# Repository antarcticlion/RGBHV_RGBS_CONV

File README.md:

# RGB MULTI CONV

Display/Monitor video signal converter PCB for Japanese Retro PC (RGBHV &lt;--> RGBS ./ etc. )

##概要

主に日本製のレトロPCのRGB信号を、コネクタ変換・信号変換・分岐を行うボードです。
Rev1.5でサブボードをスタックして扱うコネクタを増やせるようにしています。
プロジェクトにはKiCad PCB 5.0用のプロジェクトファイルとガーバーが含まれます。

##外観

## 動作確認済機種
### Video signal src.
- IBM-PC compatible (VGA)  
- PC-8801mk2 (Digital RGB 8p)  
- PC-8801mk2MR/FH (Digital RGB 8p/Analog RGB DA15)  
- PC-9801DA/U2 (Analog RGB DA15)  
- PC-9801VX41 (Digital RGB 8p/Analog RGB DA15)  
- X1 Turbo model40 (Digital RGB 8p)  
- X1 Turbo model30 (Digital RGB 6p)  
- MZ-700 (Digital RGB 8p)  
- FM-7 (Digital RGB 8p)  
- FM-new7 (Digital RGB 8p)  
- BASIC Master Level 3 (Digital RGB 8p)  
- Arcade-Game PCBs (クイズココロジー2／上海2／子育てクイズ マイエンジェル）(信号分岐、コネクタ変換)
- 上記の他、PC8001シリーズ(Digital RGB)で動作報告をいただいております。ありがとうございます。
### Video signal dst.
- GBS-8200/GBS-8220/HD9800V/HD-VC9900(RGBS)
- Some VGA monitors (DE15/VGA)

***
[概要](https://github.com/antarcticlion/RGBHV_RGBS_CONV/wiki)  
[作り方](https://github.com/antarcticlion/RGBHV_RGBS_CONV/wiki/How-to-make)  
[デザインと説明](https://github.com/antarcticlion/RGBHV_RGBS_CONV/wiki/Design)  
[その他](https://github.com/antarcticlion/RGBHV_RGBS_CONV/wiki/Miscellaneous)  
[リリースノート](https://github.com/antarcticlion/RGBHV_RGBS_CONV/wiki/Release-note)  

***
最新版 Rev1.5A

***
# Lastest Gerber

### 1.5A  
https://github.com/antarcticlion/RGBHV_RGBS_CONV/blob/master/RGBHV_RGBS_CONV_15A.zip メインボード
https://github.com/antarcticlion/RGBHV_RGBS_CONV/blob/master/RGBHV_RGBS_CONV_EXTRA1_15.zip　デジタルRGBサブボード
https://github.com/antarcticlion/RGBHV_RGBS_CONV/blob/master/RGBHV_RGBS_CONV_stack_15.zip　GBSスタック用サブボード

## Arcive

### 1.0D  
https://github.com/antarcticlion/RGBHV_RGBS_CONV/blob/master/RGBHV_RGBS_CONV_10D.zip

***
# Changes Log  
| Revision | Date | Description |
|:---|:---|:---|
|1.5A release |2022/10/03 | スイッチのスルーホールサイズを変更 |
|1.5 release candidate |2022/09/23 | DE15/DA15を残し他のコネクタは小基板化、EL1883用パターンを追加、各種切り替えスイッチを付ける |
||2022/09/23 | 最新のガーバーファイルを残して古いものは削除 |
|1.0D release |2021/07/29 | DIN8コネクタのフットプリントが裏表逆になっていたのをFIX |
|1.0C release |2021/07/09 | RGBSへの音声パターンカット、レギュレータの足配置バリエーションの追加 |
|1.0B release |2021/05/11 | 3.3Vレギュレータによる電源安定化、3.3V駆動の5VトレラントCMOSロジックでGBS出力の無調整化(SN74AHC86N推奨) |
|0.5B release |2020/06/10 | RGBS出力に多回転VRを追加し、出力レベルを下げられるコネクタを用意。(GBS8200/8220のCSYNC信号不安定対策) |
|0.5A release |2019/08/28 | あまり使わないコネクタと、動悸分離回路を削除、RGBHV DA15のエッジ端コネクタを追加 |
|0.4A release candidate |2019/03/04 | コネクタ位置調整、DCジャック追加 |
|0.4 |2019/03/04 | first release. (experimental) |
|0.1～0.3 | N/A | private |

***
# ライセンス

2022/06/04 
Rev1.0D以降のライセンスを CERN Open Hardware Licence Version 2 - Weakly Reciprocal に変更します。
以前のバージョンのアーカイブは近日消します。

https://spdx.org/licenses/CERN-OHL-W-2.0.html
PDF https://github.com/antarcticlion/RGBHV_RGBS_CONV/blob/master/cern_ohl_w_v2.pdf
HOWTO https://github.com/antarcticlion/RGBHV_RGBS_CONV/blob/master/cern_ohl_w_v2_howto.pdf

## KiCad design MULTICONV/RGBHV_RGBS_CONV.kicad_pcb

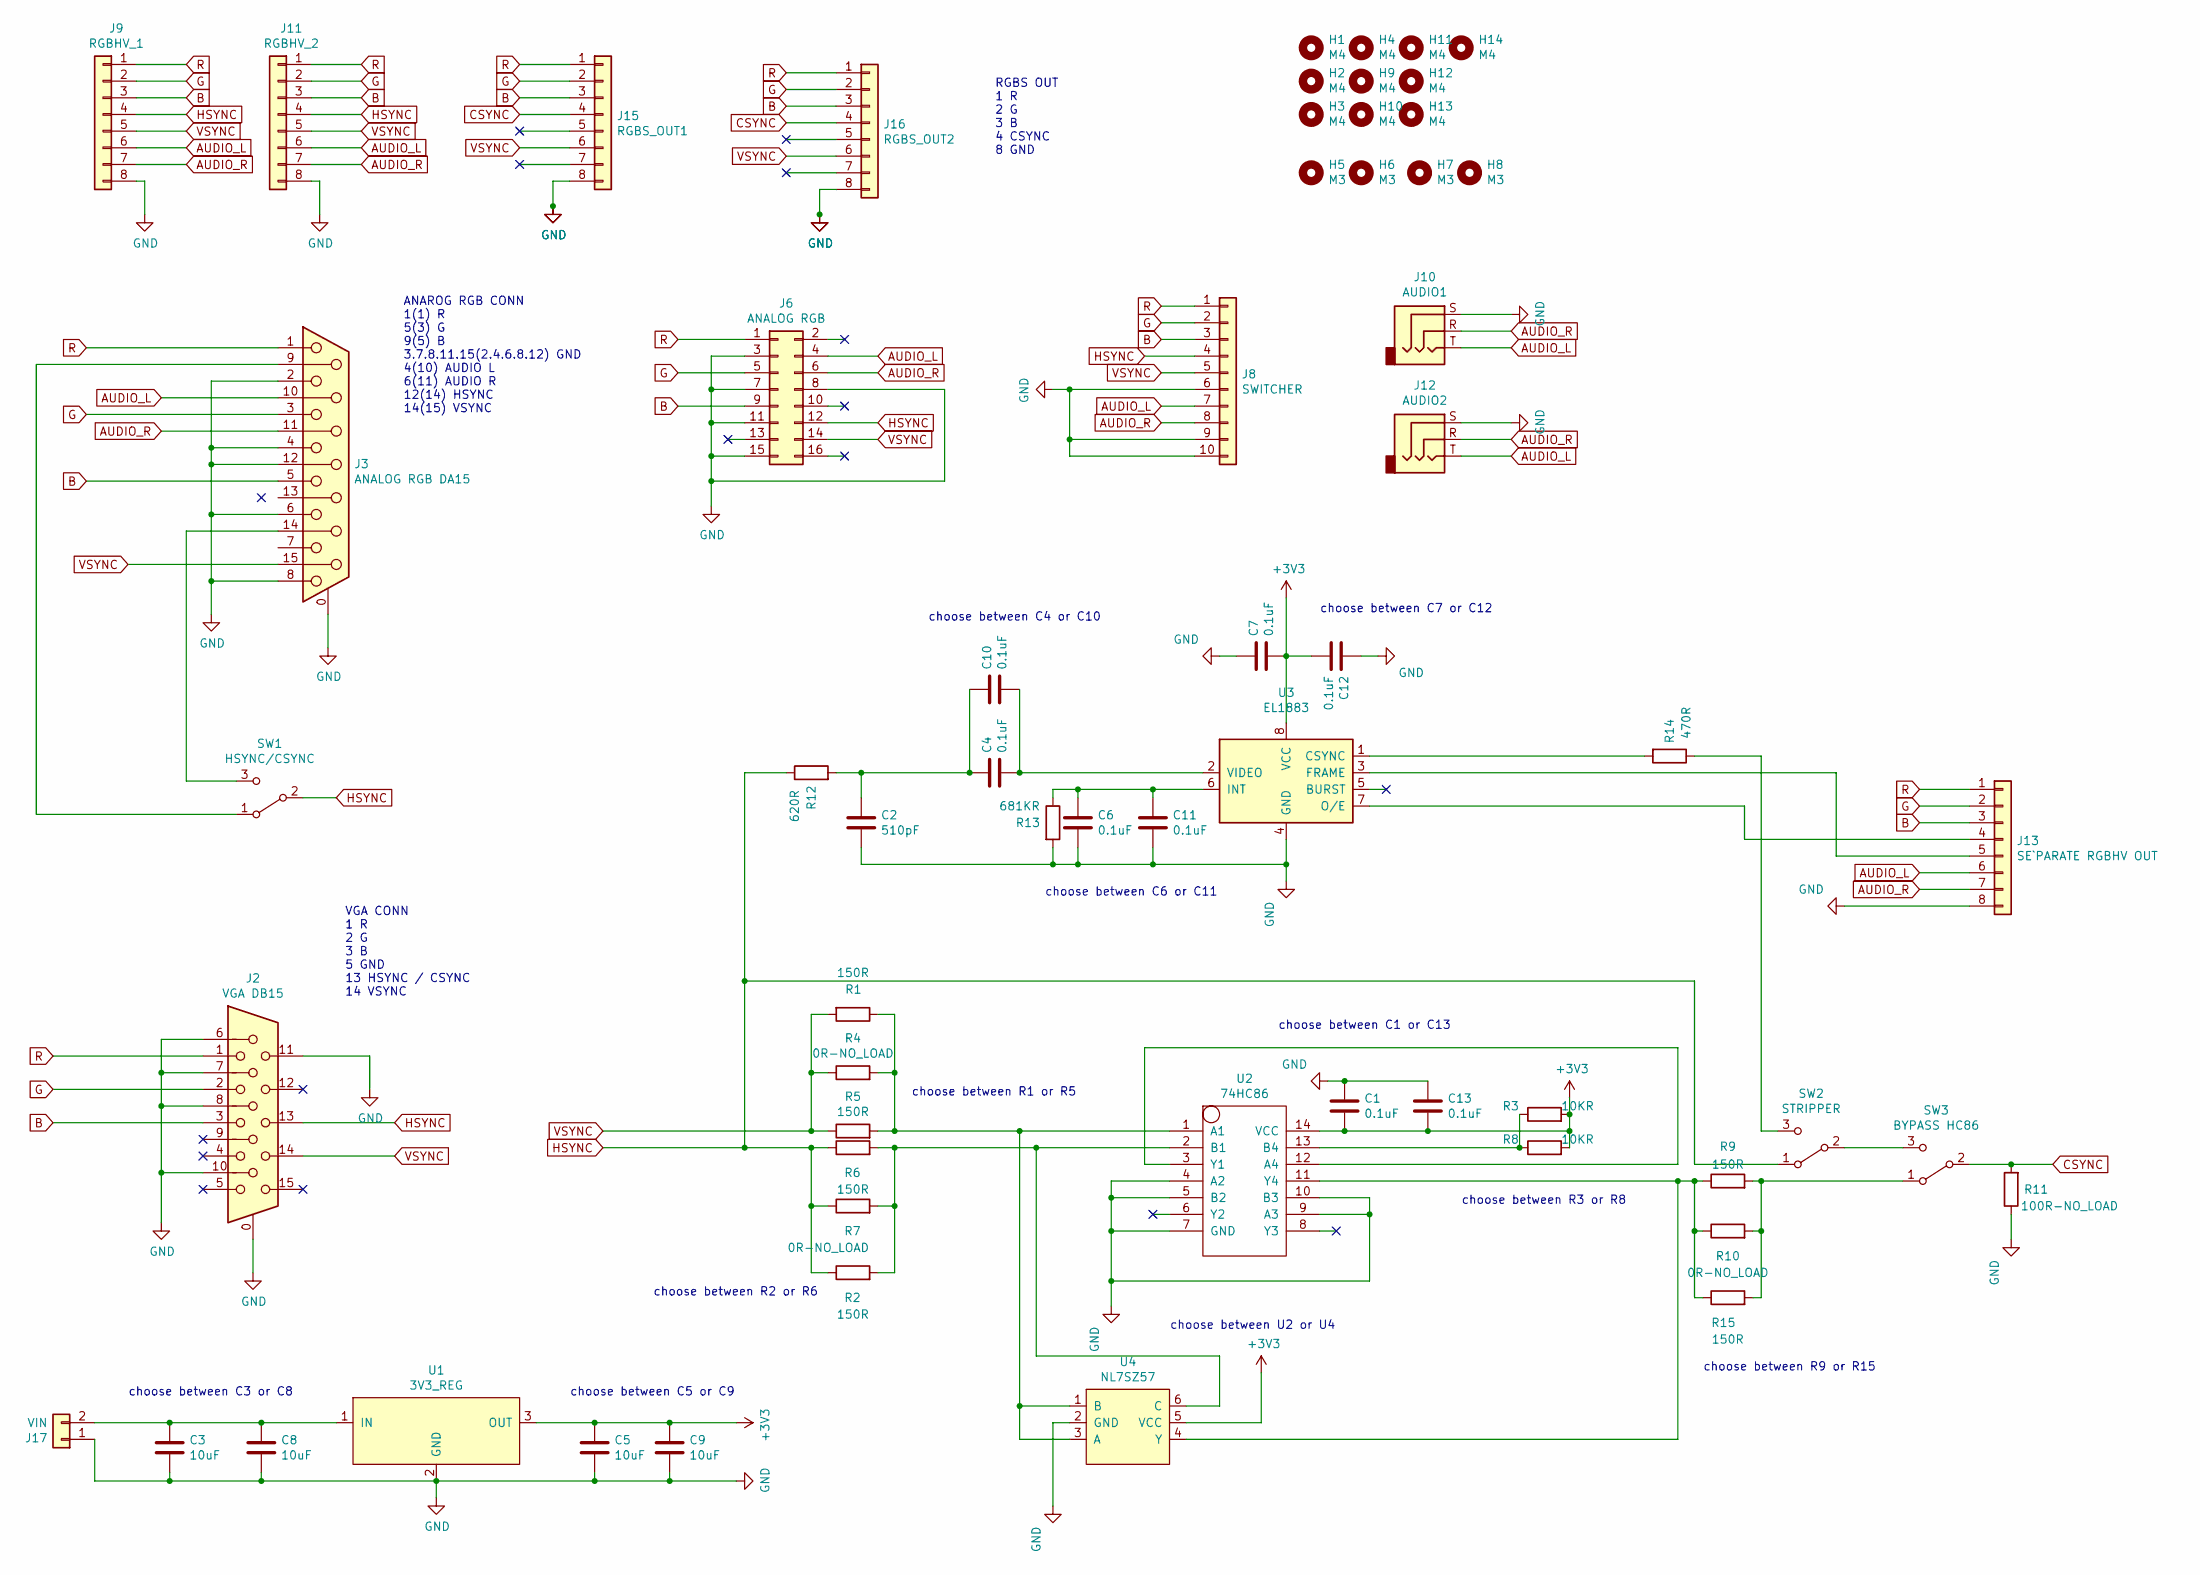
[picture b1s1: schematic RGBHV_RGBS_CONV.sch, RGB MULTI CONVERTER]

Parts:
C1, C4, C6, C7: 0.1uF; C_Disc_D5.0mm_W2.5mm_P5.00mm
C2: 510pF; C_Disc_D5.0mm_W2.5mm_P5.00mm
C3, C5: 10uF; C_Disc_D5.0mm_W2.5mm_P5.00mm
C8, C9: 10uF; C_1206_3216Metric
C10, C11, C12, C13: 0.1uF; C_0603_1608Metric
H1, H2, H3, H4, H9, H10, H11, H12, H13, H14: M4; MountingHole_4.3mm_M4
H5, H6, H7, H8: M3; MountingHole_3.2mm_M3
J2: VGA DB15; DB_15F-VGA_L
J3: ANALOG RGB DA15; DSUB-15_Female_Horizontal_P2.77x2.84mm_EdgePinOffset4.94mm_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
J6: ANALOG RGB; IDC-Header_2x08_P2.54mm_Vertical
J8: SWITCHER; IDC-Header_2x05_P2.54mm_Vertical
J9: RGBHV_1; JST_XH_B8B-XH-A_1x08_P2.50mm_Vertical
J10: AUDIO1; PJ-3900-04
J11: RGBHV_2; JST_XH_B8B-XH-A_1x08_P2.50mm_Vertical
J12: AUDIO2; PJ-3900-04
J13: SE`PARATE RGBHV OUT; JST_XH_B8B-XH-A_1x08_P2.50mm_Vertical
J15: RGBS_OUT1; JST_XH_B8B-XH-A_1x08_P2.50mm_Vertical
J16: RGBS_OUT2; JST_XH_S8B-XH-A_1x08_P2.50mm_Horizontal
J17: VIN; JST_XH_S2B-XH-A_1x02_P2.50mm_Horizontal
R1, R2, R15: 150R; R_0603_1608Metric
R3: 10KR; R_0603_1608Metric
R4, R7, R10: 0R-NO_LOAD; R_Axial_DIN0207_L6.3mm_D2.5mm_P10.16mm_Horizontal
R5, R6, R9: 150R; R_Axial_DIN0207_L6.3mm_D2.5mm_P10.16mm_Horizontal
R8: 10KR; R_Axial_DIN0207_L6.3mm_D2.5mm_P10.16mm_Horizontal
R11: 100R-NO_LOAD; R_Axial_DIN0207_L6.3mm_D2.5mm_P10.16mm_Horizontal
R12: 620R; R_Axial_DIN0207_L6.3mm_D2.5mm_P10.16mm_Horizontal
R13: 681KR; R_Axial_DIN0207_L6.3mm_D2.5mm_P10.16mm_Horizontal
R14: 470R; R_Axial_DIN0207_L6.3mm_D2.5mm_P10.16mm_Horizontal
SW1: HSYNC/CSYNC; 2MS1T1B4M7QES
SW2: STRIPPER; 2MS1T1B4M7QES
SW3: BYPASS HC86; 2MS1T1B4M7QES
U1: 3V3_REG; PIN_Unified_LDO
U2: 74HC86; DIP-14_W7.62mm
U3: EL1883; SOIC-8_3.9x4.9mm_P1.27mm
U4: NL7SZ57; TSOP-6_1.65x3.05mm_P0.95mm

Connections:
+3V3: C1.2, C5.1, C7.2, C9.1, C12.2, C13.2, R3.2, R8.2, U1.3 (OUT), U2.14 (VCC), U3.8 (VCC), U4.5 (VCC)
AUDIO_L: J3.10, J6.4, J8.7, J9.6, J10.T, J11.6, J12.T, J13.6
AUDIO_R: J3.11 (P111), J6.6, J8.8, J9.7, J10.R, J11.7, J12.R, J13.7
B: J2.3, J3.5, J6.9, J8.3, J9.3, J11.3, J13.3, J15.3, J16.3
CSYNC: J15.4, J16.4, R11.2, SW3.2 (B)
G: J2.2, J3.3, J6.5, J8.2, J9.2, J11.2, J13.2, J15.2, J16.2
GND: C1.1, C2.2, C3.2, C5.2, C6.2, C7.1, C8.2, C9.2, C11.2, C12.1, C13.1, J2.0, J2.6, J2.7, J2.8, J2.10, J2.11, J3.0 (PAD), J3.2, J3.4, J3.6, J3.8, J3.12, J6.3, J6.7, J6.8, J6.11, J6.15, J8.6, J8.9, J8.10, J9.8, J10.S, J11.8, J12.S, J13.8, J15.8, J16.8, J17.1, R11.1, R13.2, U1.2 (GND), U2.4 (A2), U2.5 (B2), U2.7 (GND), U2.9 (A3), U2.10 (B3), U3.4 (GND), U4.2 (GND)
HSYNC: J2.13, J6.12, J8.4, J9.4, J11.4, R2.1, R6.1, R7.1, R12.1, SW1.2 (B), SW2.1 (A)
unnamed: C3.1, C8.1, J17.2, U1.1 (IN)
unnamed: C2.1, C4.1, C10.1, R12.2
unnamed: C4.2, C10.2, U3.2 (VIDEO)
unnamed: C6.1, C11.1, R13.1, U3.6 (INT)
unnamed: J3.9, SW1.1 (A)
unnamed: J3.14, SW1.3 (C)
unnamed: J13.4, U3.7 (O/E)
unnamed: J13.5, U3.3 (FRAME)
unnamed: R1.1, R4.2, R5.2, U2.1 (A1), U4.1 (B), U4.3 (A)
unnamed: R2.2, R6.2, R7.2, U2.2 (B1), U4.6 (C)
unnamed: R3.1, R8.1, U2.13 (B4)
unnamed: R9.1, R10.1, R15.1, U2.11 (Y4), U4.4 (Y)
unnamed: R9.2, R10.2, R15.2, SW3.1 (A)
unnamed: R14.1, SW2.3 (C)
unnamed: R14.2, U3.1 (CSYNC)
unnamed: SW2.2 (B), SW3.3 (C)
unnamed: U2.3 (Y1), U2.12 (A4)
R: J2.1, J3.1, J6.1, J8.1, J9.1, J11.1, J13.1, J15.1, J16.1
VSYNC: J2.14, J3.15, J6.14, J8.5, J9.5, J11.5, J15.6, J16.6, R1.2, R4.1, R5.1

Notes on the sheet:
ANAROG RGB CONN 1(1) R 5(3) G 9(5) B 3.7.8.11.15(2.4.6.8.12) GND 4(10) AUDIO L 6(11) AUDIO R 12(14) HSYNC 14(15) VSYNC
RGBS OUT 1 R 2 G 3 B 4 CSYNC 8 GND
VGA CONN 1 R 2 G 3 B 5 GND 13 HSYNC / CSYNC 14 VSYNC
choose between R1 or R5
choose between R2 or R6
choose between U2 or U4
choose between C1 or C13
choose between R3 or R8
choose between R9 or R15
choose between C7 or C12
choose between C4 or C10
choose between C6 or C11
choose between C5 or C9
choose between C3 or C8

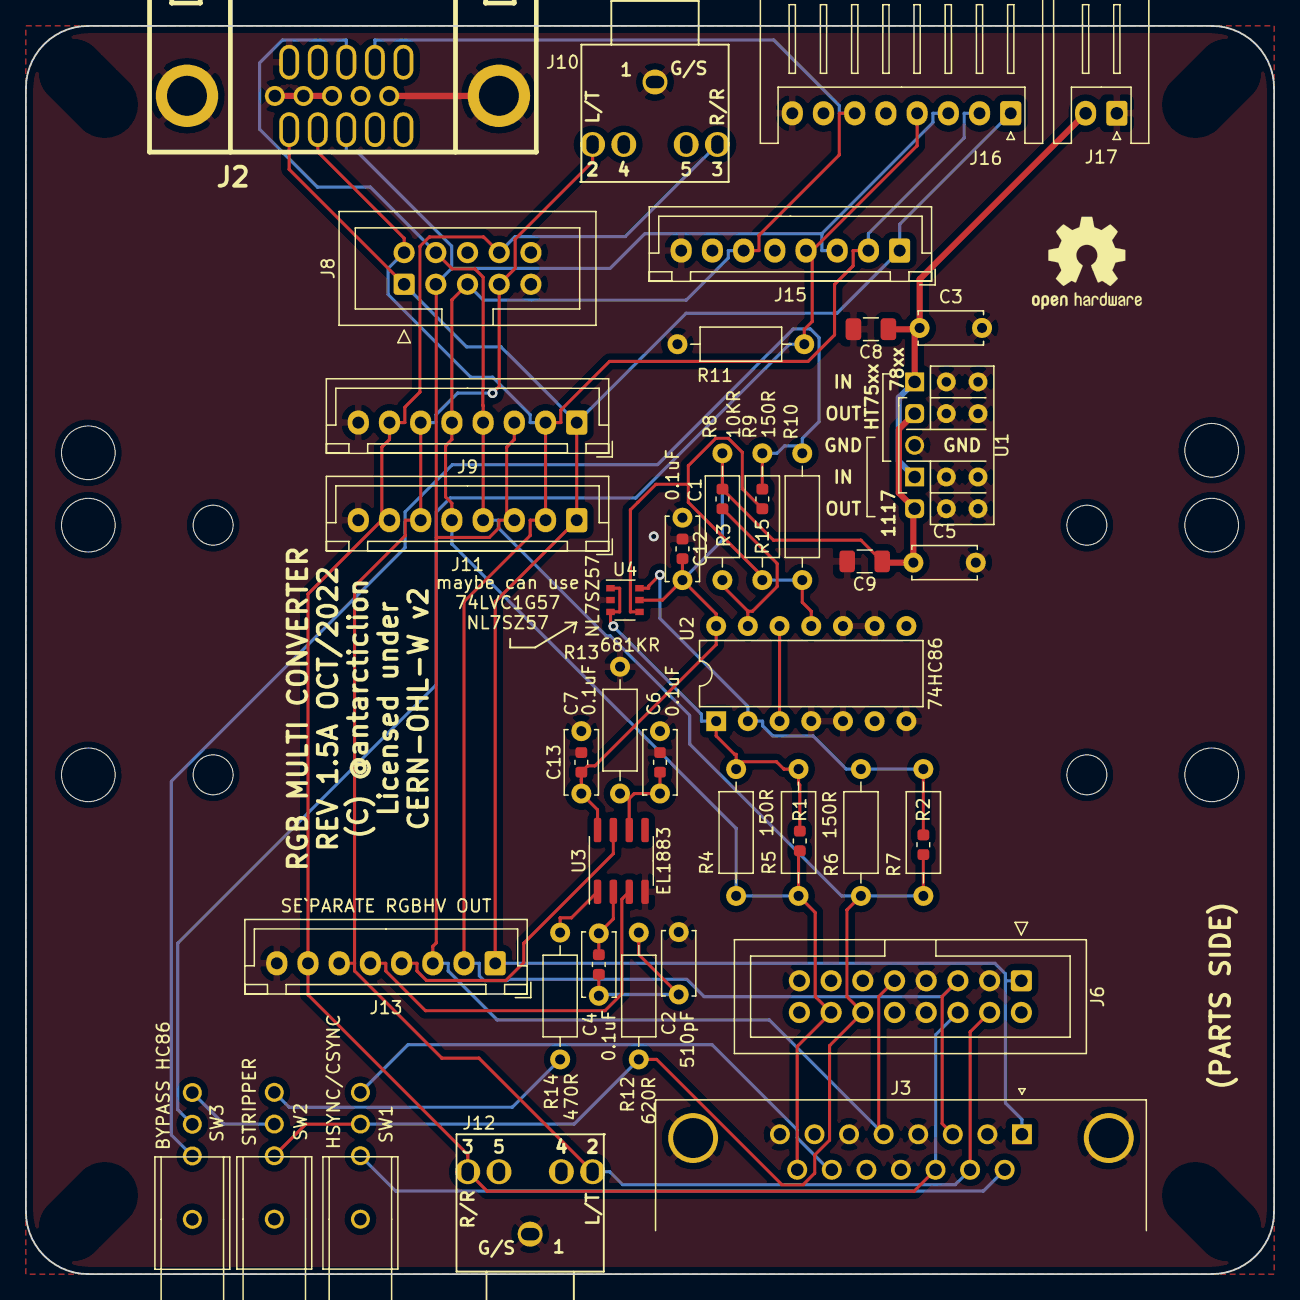
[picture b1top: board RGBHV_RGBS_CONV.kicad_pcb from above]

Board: 2 copper layers, 100.0 x 100.0 mm, 61 parts (0 on the bottom side), 27 nets.

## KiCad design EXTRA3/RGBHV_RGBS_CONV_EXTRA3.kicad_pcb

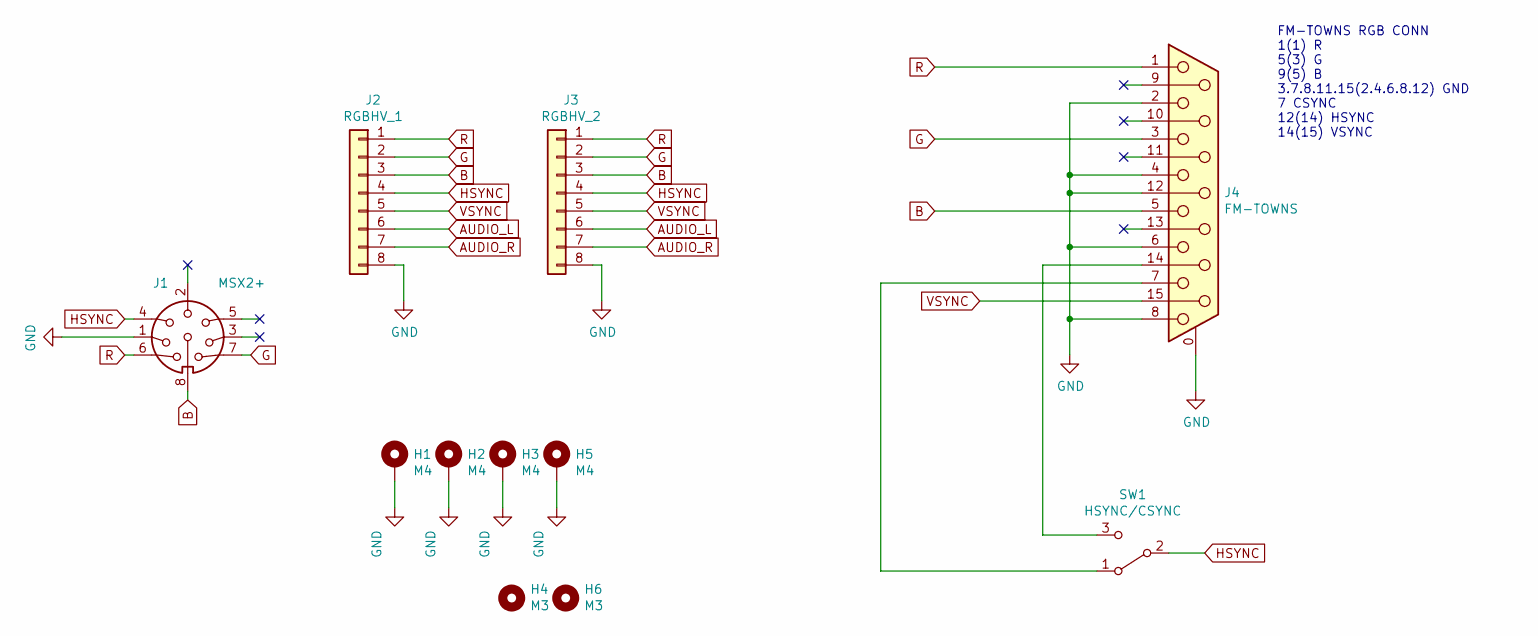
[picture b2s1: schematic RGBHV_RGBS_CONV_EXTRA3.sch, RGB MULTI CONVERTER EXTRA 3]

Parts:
H1, H2, H3, H5: M4; MountingHole_4.3mm_M4_Pad
H4, H6: M3; MountingHole_3.2mm_M3
J1: MSX2+; DIN 8 PCB
J2: RGBHV_1; JST_XH_B8B-XH-A_1x08_P2.50mm_Vertical
J3: RGBHV_2; JST_XH_B8B-XH-A_1x08_P2.50mm_Vertical
J4: FM-TOWNS; DSUB-15_Female_Horizontal_P2.77x2.84mm_EdgePinOffset4.94mm_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
SW1: HSYNC/CSYNC; 2MS1T1B4M7QES

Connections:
AUDIO_L: J2.6, J3.6
AUDIO_R: J2.7, J3.7
B: J1.8, J2.3, J3.3, J4.5
G: J1.7, J2.2, J3.2, J4.3
GND: H1.1, H2.1, H3.1, H5.1, J1.1, J2.8, J3.8, J4.0 (PAD), J4.2, J4.4, J4.6, J4.8, J4.12
HSYNC: J1.4, J2.4, J3.4, SW1.2 (B)
unnamed: J4.7, SW1.1 (A)
unnamed: J4.14, SW1.3 (C)
R: J1.6, J2.1, J3.1, J4.1
VSYNC: J2.5, J3.5, J4.15

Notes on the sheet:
FM-TOWNS RGB CONN 1(1) R 5(3) G 9(5) B 3.7.8.11.15(2.4.6.8.12) GND 7 CSYNC 12(14) HSYNC 14(15) VSYNC

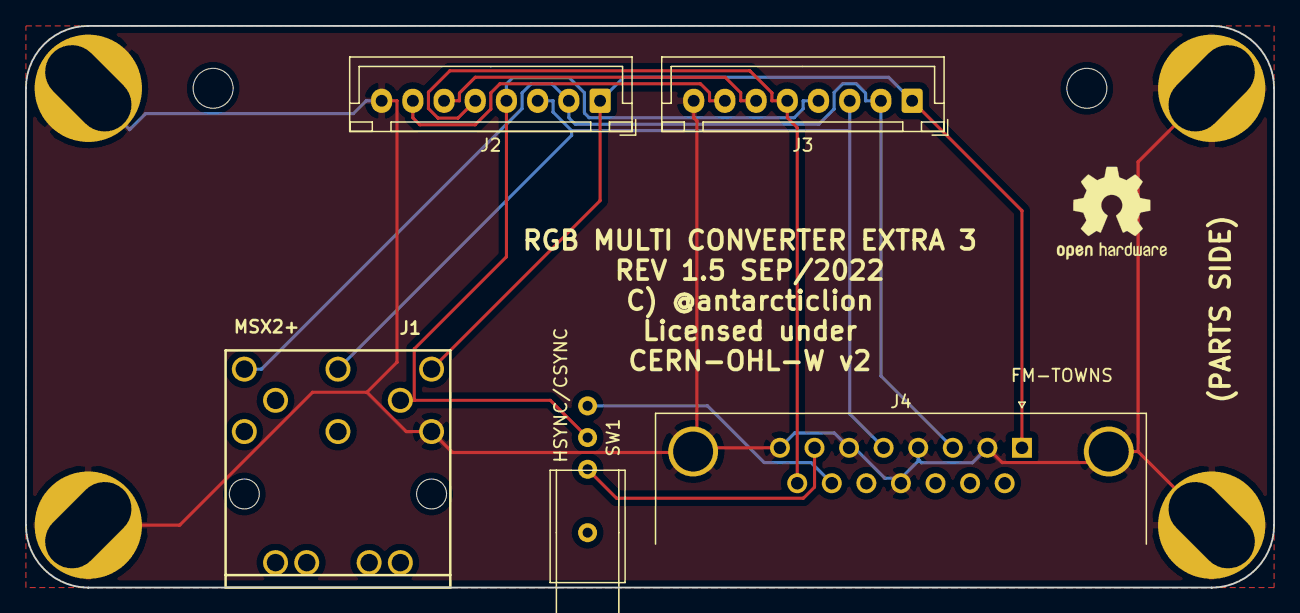
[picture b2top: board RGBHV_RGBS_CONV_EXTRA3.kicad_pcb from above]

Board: 2 copper layers, 100.0 x 45.0 mm, 11 parts (0 on the bottom side), 10 nets.

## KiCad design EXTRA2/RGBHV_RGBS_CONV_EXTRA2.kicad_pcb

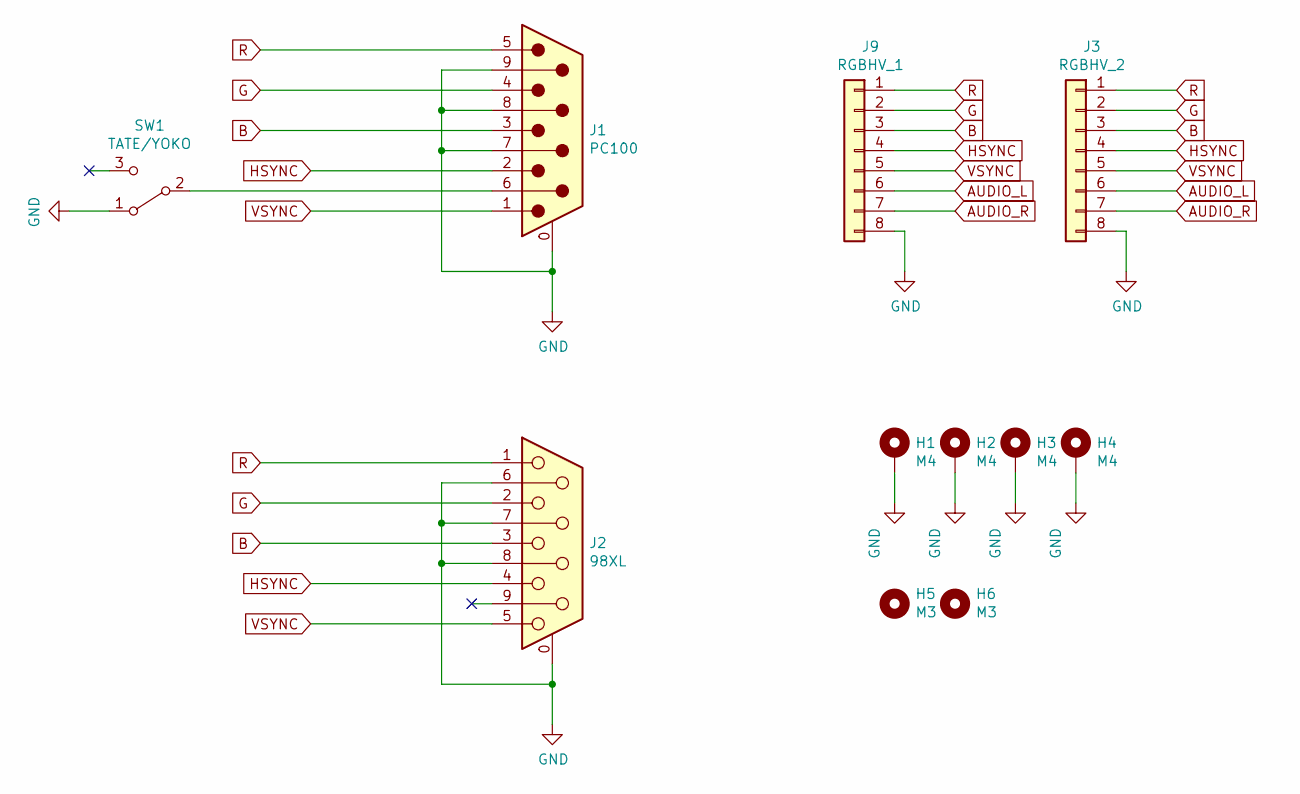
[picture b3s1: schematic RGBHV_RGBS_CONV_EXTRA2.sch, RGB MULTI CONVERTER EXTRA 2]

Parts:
H1, H2, H3, H4: M4; MountingHole_4.3mm_M4_Pad
H5, H6: M3; MountingHole_3.2mm_M3
J1: PC100; DSUB-9_Male_Horizontal_P2.77x2.84mm_EdgePinOffset4.94mm_Hou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
J2: 98XL; DSUB-9_Female_Horizontal_P2.77x2.84mm_EdgePinOffset4.94mm_H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
J3: RGBHV_2; JST_XH_B8B-XH-A_1x08_P2.50mm_Vertical
J9: RGBHV_1; JST_XH_B8B-XH-A_1x08_P2.50mm_Vertical
SW1: TATE/YOKO; 2MS1T1B4M7QES

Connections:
AUDIO_L: J3.6, J9.6
AUDIO_R: J3.7, J9.7
B: J1.3, J2.3, J3.3, J9.3
G: J1.4, J2.2, J3.2, J9.2
GND: H1.1, H2.1, H3.1, H4.1, J1.0 (PAD), J1.7, J1.8, J1.9, J2.0 (PAD), J2.6, J2.7, J2.8, J3.8, J9.8, SW1.1 (A)
HSYNC: J1.2, J2.4, J3.4, J9.4
unnamed: J1.6, SW1.2 (B)
R: J1.5, J2.1, J3.1, J9.1
VSYNC: J1.1, J2.5, J3.5, J9.5

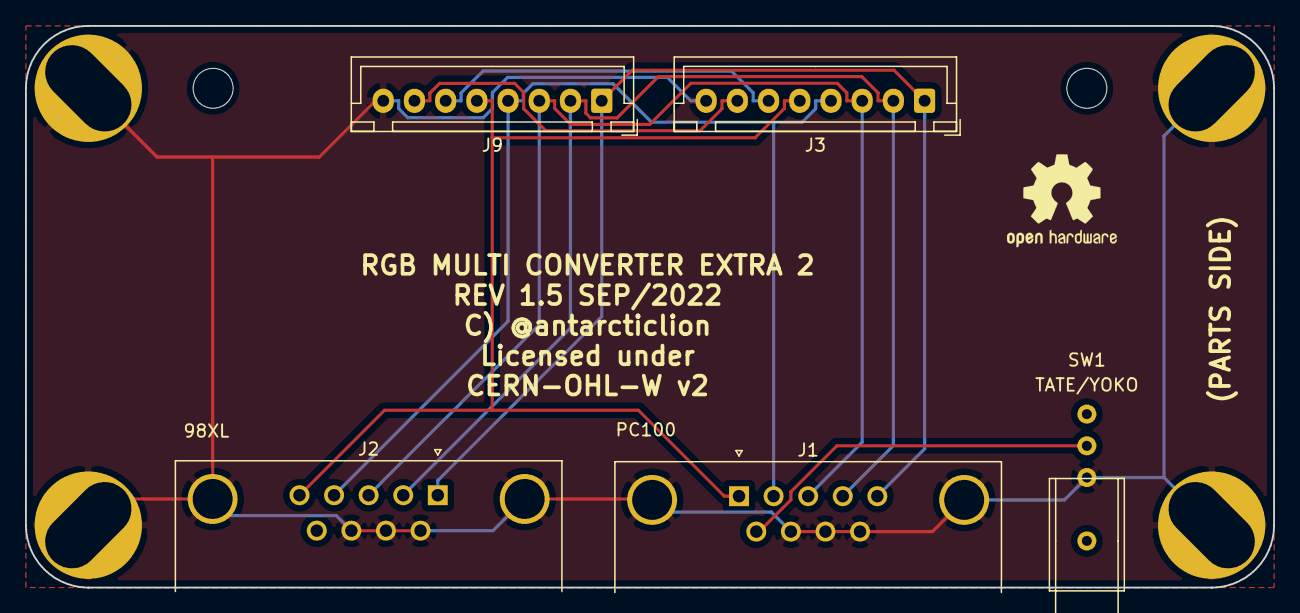
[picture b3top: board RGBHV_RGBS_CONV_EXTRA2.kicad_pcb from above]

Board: 2 copper layers, 100.0 x 45.0 mm, 11 parts (0 on the bottom side), 9 nets.

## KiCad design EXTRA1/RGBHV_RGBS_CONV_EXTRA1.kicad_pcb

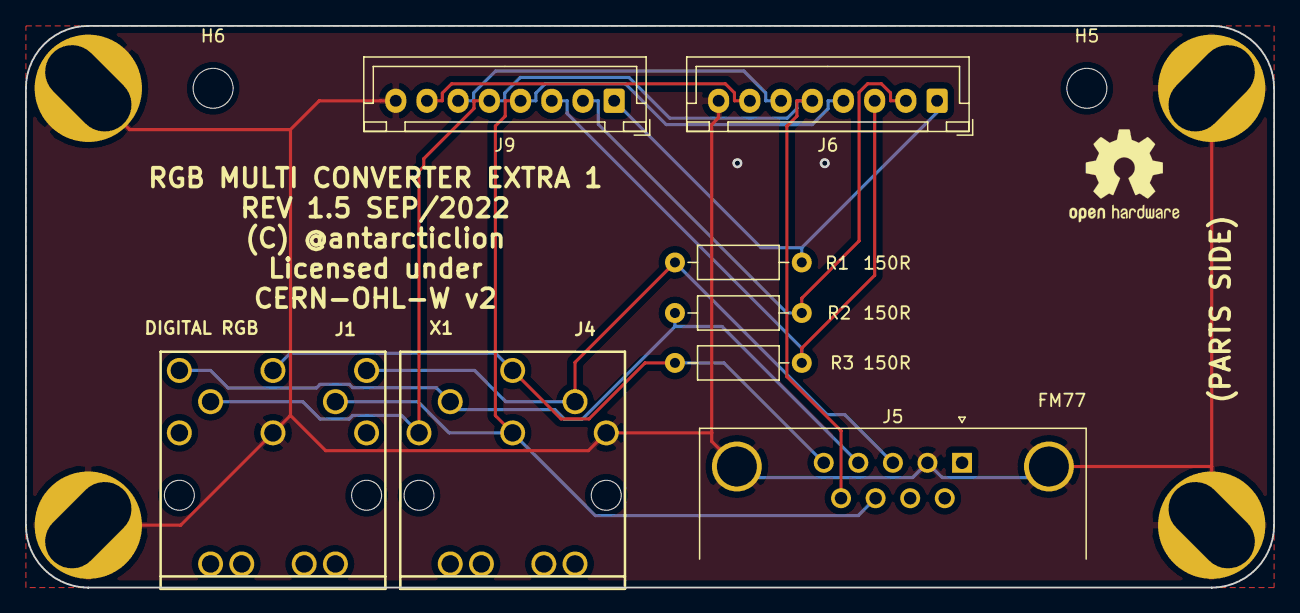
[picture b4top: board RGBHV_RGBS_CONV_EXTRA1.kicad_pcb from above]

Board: 2 copper layers, 100.0 x 45.0 mm, 16 parts (1 on the bottom side), 11 nets.

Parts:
H1, H2, H3, H4: M4; MountingHole_4.3mm_M4_Pad
H5, H6: M3; MountingHole_3.2mm_M3
J1: DIGITAL RGB; DIN 8 PCB
J4: X1; DIN_6_PCB
J5: FM77; DSUB-9_Female_Horizontal_P2.77x2.84mm_EdgePinOffset4.94mm_H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
J6: RGBHV_2; JST_XH_B8B-XH-A_1x08_P2.50mm_Vertical
J9: RGBHV_1; JST_XH_B8B-XH-A_1x08_P2.50mm_Vertical
LOGO1, LOGO1#2: OSHW-Logo2_9.8x8mm_SilkScreen
R1, R2, R3: 150R; R_Axial_DIN0207_L6.3mm_D2.5mm_P10.16mm_Horizontal

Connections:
AUDIO_L: J6.6, J9.6
AUDIO_R: J6.7, J9.7
B: J6.3, J9.3, R3.2
DIGITAL_B: J1.8, J4.6, J5.5, R3.1
DIGITAL_G: J1.7, J4.4, J5.4, R2.1
DIGITAL_R: J1.6, J4.2, J5.3, R1.1
G: J6.2, J9.2, R2.2
GND: H1.1, H2.1, H3.1, H4.1, J1.2, J4.1, J5.0, J5.2, J6.8, J9.8
HSYNC: J1.4, J4.3, J5.8, J6.4, J9.4
R: J6.1, J9.1, R1.2
VSYNC: J1.5, J4.5, J5.9, J6.5, J9.5

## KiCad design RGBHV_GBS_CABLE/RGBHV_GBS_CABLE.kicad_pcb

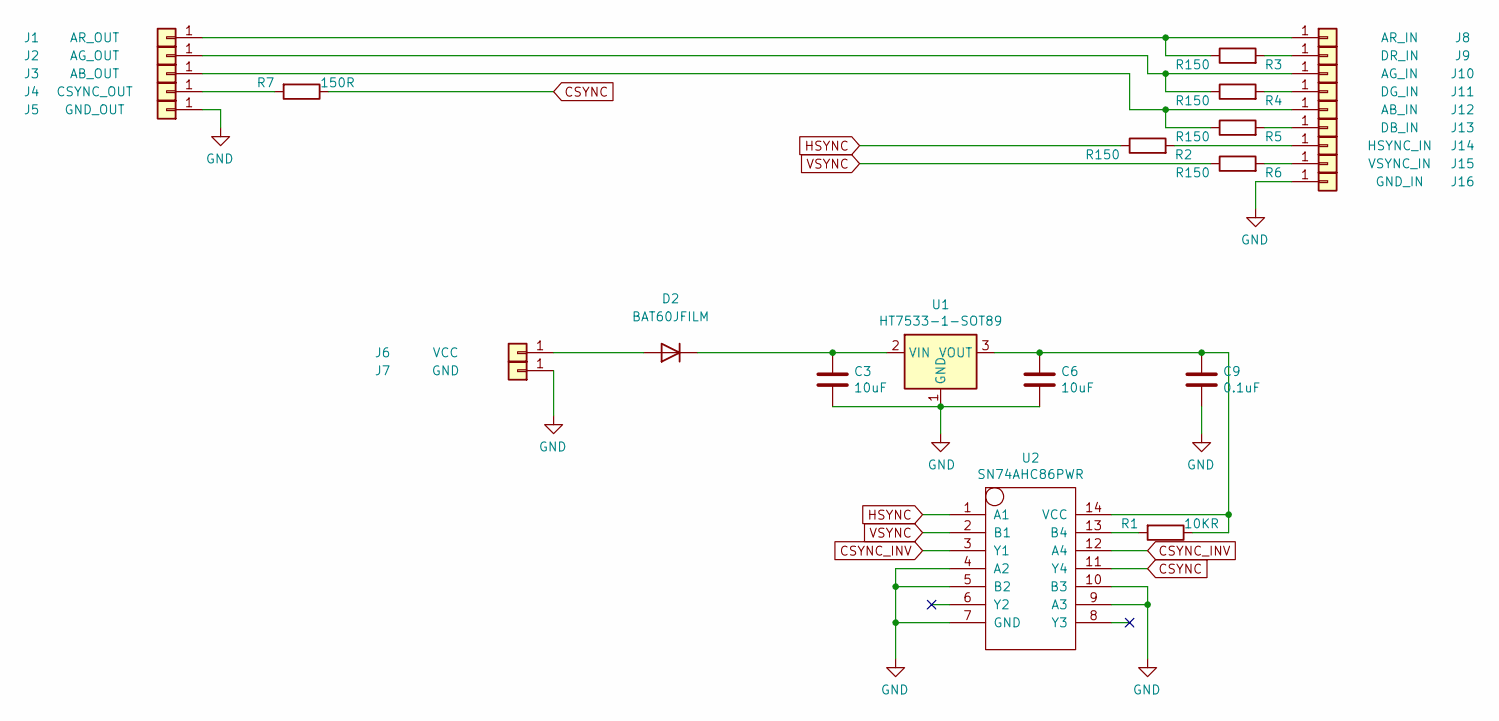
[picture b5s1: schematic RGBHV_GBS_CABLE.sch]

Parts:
C3, C6: 10uF; C_0805_2012Metric
C9: 0.1uF; C_0402_1005Metric
D2: BAT60JFILM; D_SOD-323
J1: AR_OUT; PAD
J2: AG_OUT; PAD
J3: AB_OUT; PAD
J4: CSYNC_OUT; PAD
J5: GND_OUT; PAD
J6: VCC; PAD
J7: GND; PAD
J8: AR_IN; PAD
J9: DR_IN; PAD
J10: AG_IN; PAD
J11: DG_IN; PAD
J12: AB_IN; PAD
J13: DB_IN; PAD
J14: HSYNC_IN; PAD
J15: VSYNC_IN; PAD
J16: GND_IN; PAD
R1: 10KR; R_0402_1005Metric
R2, R3, R4, R5, R6: R150; R_0402_1005Metric
R7: 150R; R_0402_1005Metric
U1: HT7533-1-SOT89; SOT-89-3
U2: SN74AHC86PWR; TSSOP-14_4.4x5mm_P0.65mm

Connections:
CSYNC: R7.1, U2.11 (Y4)
CSYNC_INV: U2.3 (Y1), U2.12 (A4)
GND: C3.2, C6.2, C9.2, J5.1, J7.1, J16.1, U1.1 (GND), U2.4 (A2), U2.5 (B2), U2.7 (GND), U2.9 (A3), U2.10 (B3)
HSYNC: R2.1, U2.1 (A1)
unnamed: C3.1, D2.1 (K), U1.2 (VIN)
unnamed: C6.1, C9.1, R1.1, U1.3 (VOUT), U2.14 (VCC)
unnamed: D2.2 (A), J6.1
unnamed: J1.1, J8.1, R3.1
unnamed: J4.1, R7.2
unnamed: J9.1, R3.2
unnamed: J2.1, J10.1, R4.1
unnamed: J11.1, R4.2
unnamed: J3.1, J12.1, R5.1
unnamed: J13.1, R5.2
unnamed: J14.1, R2.2
unnamed: J15.1, R6.2
unnamed: R1.2, U2.13 (B4)
VSYNC: R6.1, U2.2 (B1)

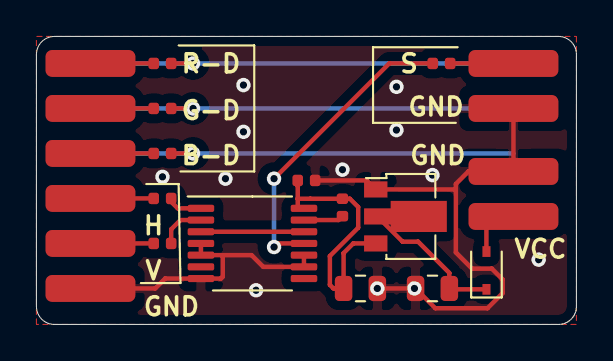
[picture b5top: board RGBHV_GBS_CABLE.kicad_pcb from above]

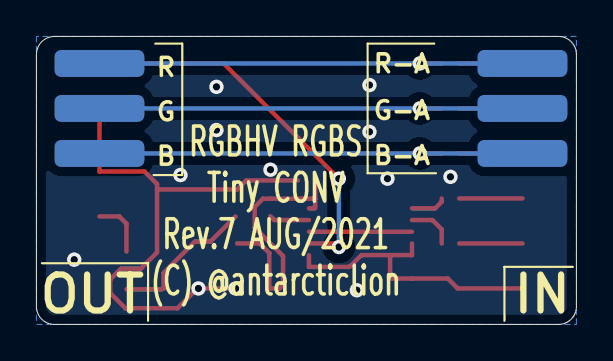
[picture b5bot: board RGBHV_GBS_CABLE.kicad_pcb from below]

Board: 2 copper layers, 30.0 x 16.0 mm, 29 parts (6 on the bottom side), 18 nets.

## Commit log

2019-03-03 Initial upload
2019-03-03 訂正
    ✕ とりあえずJ14とJ10にジャンパを付けてください。
    〇 とりあえずJ14とJ13にジャンパを付けてください。
2019-03-04 訂正
    ✕ Rev0.4b
    〇 Rev0.4a
2019-03-31 Rev0.4 DIN6(for X1) confirmed.
2019-08-28 Rev.5A DIn8 fix and remove sync sep.
2019-08-28 Rev5A
2020-03-25 Rev.5B add VR to RGBS OUT
2020-03-25 Rev 0.5B pre-release
    説明を書いている時間が無いので取り急ぎ検証済みのガーバーデータだけ。
2020-06-09 Rev.5B Add RGBS VR
2020-06-09 Rev.5B
2021-05-11 initial upload
    Rev 1.0B gerber
2021-05-11 Rev1.0B
2021-07-09 Rev1.0C
    レギュレータのパターンを追加。
    RGBS XHコネクタへの音声パターンカット
2021-07-09 Rev1.0C
2021-07-29 Rev 1.0D
    Fix DIN8 R-G H-V pin swap bug
2021-07-29 Rev1.0D
    Fix DIN8 R-G H-V pin swap bug
2021-08-23 add RGBHV_GBS_CABLE
    ケーブル中継ケースに内蔵する子基板を追加
2021-09-11 Initial upload
    Stack plate to mount conv pcb on GBS
2022-06-04 Licence update
    Licence change to CERN Open Hardware Licence Version 2 - Weakly Reciprocal
2022-06-04 Licence update
2022-09-22 Delete RGBHV_RGBS_CONV05A.zip
    旧ファイルの削除
2022-09-22 Delete RGBHV_RGBS_CONV05B.zip
    旧ファイルの削除
2022-09-22 Delete RGBHV_RGBS_CONV_04.zip
    旧ファイルの削除
2022-09-22 Delete RGBHV_RGBS_CONV_04A.zip
    旧ファイルの削除
2022-09-22 Delete RGBHV_RGBS_CONV_10B2.zip
    旧ファイルの削除
2022-09-22 Delete RGBHV_RGBS_CONV_10C.zip
    旧ファイルの削除
2022-09-22 格納位置変更のため再アップロード
2022-09-22 Rev1.5 リリース候補
2022-09-22 Rev1.5リリース候補
2022-10-03 Fix switch hole size
2022-10-03 Rev 1.5A
2022-10-03 Rev 1.5A release
2022-10-04 錯誤の修正

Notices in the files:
EXTRA1/RGBHV_RGBS_CONV_EXTRA1.kicad_pcb:
Licensed under
CERN-OHL-W v2
EXTRA2/RGBHV_RGBS_CONV_EXTRA2.sch:
Licensed under CERN-OHL-W v2
RGBHV_RGBS_CONV.sch:
License : CC BY SA 4.0
